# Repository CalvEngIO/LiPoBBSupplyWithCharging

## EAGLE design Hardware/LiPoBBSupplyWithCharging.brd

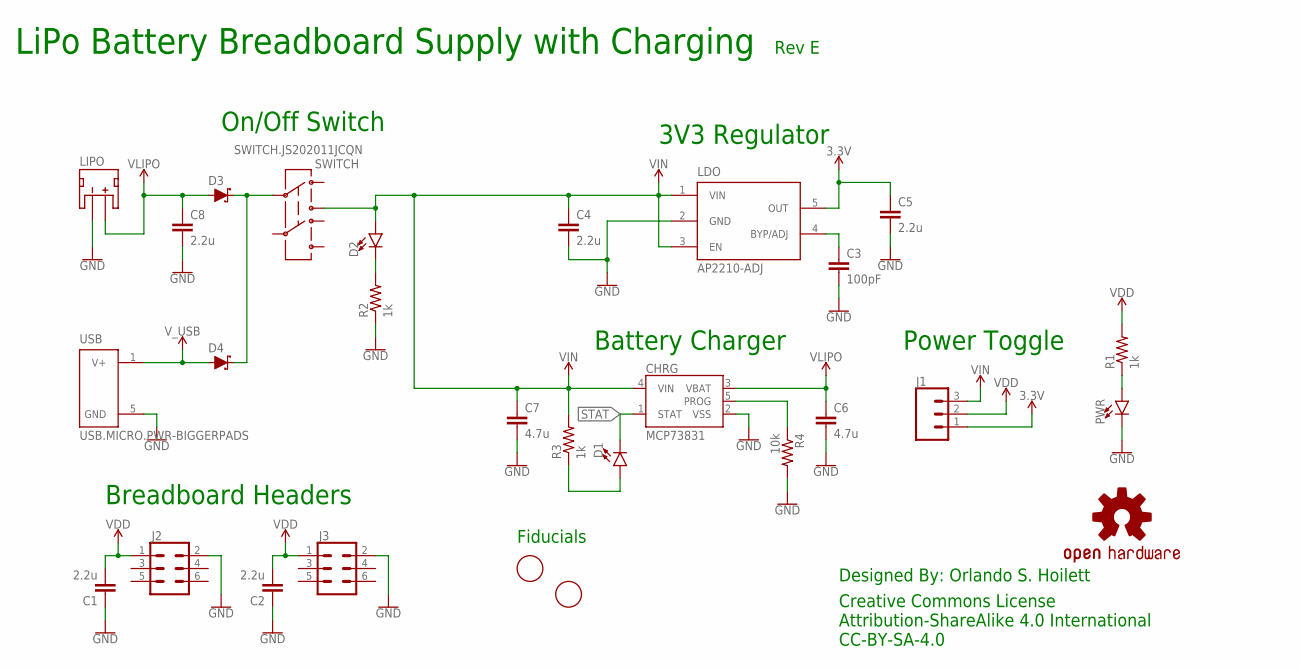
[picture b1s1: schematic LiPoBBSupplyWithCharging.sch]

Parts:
C1, C2, C4, C5, C8: 2.2u; C0603
C3: 100pF; C0402
C6, C7: 4.7u; C0603
CHRG: MCP73831; SOT23-5
D1, D2: LED0603; LED-0603
D3, D4: SCHOTTKY-USC; USC
FD1, FD2: FIDUCIAL; FIDUCIAL_1MM
J1: CONN_03; 1X03
J2, J3: CONN_03X22X3_SILK_MALE_PTH; 2X3
LDO: AP2210-ADJ; SOT23-5
LIPO: JST_2MM_MALE; JST-2-SMD
LOGO1: OSHW-LOGOS; OSHW-LOGO-S
PWR: LED0603; LED-0603
R1, R2, R3: 1k; R0402
R4: 10k; R0402
SWITCH: SWITCH.JS202011JCQN; SWITCH.00
U$1: HANDLE.1HANDLE.025; HANDLE.025
U$3: CALVENGIO_HANDLEHANDLE.1; CALVENGIO_HANDLE.1
USB: USB.MICRO.PWR-BIGGERPADS; USB-MICRO-01.BIGGERPADS.PWR

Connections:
3.3V: C5.1, J1.1, LDO.5 (OUT)
GND: C1.1, C2.1, C3.2, C4.2, C5.2, C6.2, C7.2, C8.2, CHRG.2 (VSS), J2.2, J3.2, LDO.2 (GND), LIPO.1 (-), PWR.C, R2.1, R4.2, USB.5 (GND)
unnamed: PWR.A, R1.1
unnamed: D2.C, R2.2
unnamed: C3.1, LDO.4 (BYP/ADJ)
unnamed: D1.A, R3.1
unnamed: CHRG.5 (PROG), R4.1
unnamed: D3.- (C), D4.- (C), SWITCH.2
STAT: CHRG.1 (STAT), D1.C
VDD: C1.2, C2.2, J1.2, J2.1, J3.1, R1.2
VIN: C4.1, C7.1, CHRG.4 (VIN), D2.A, J1.3, LDO.1 (VIN), LDO.3 (EN), R3.2, SWITCH.3
VLIPO: C6.1, C8.1, CHRG.3 (VBAT), D3.+ (A), LIPO.2 (+)
V_USB: D4.+ (A), USB.1 (V+)

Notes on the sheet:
Breadboard Headers
Power Toggle
3V3 Regulator
On/Off Switch
Fiducials
Creative Commons License Attribution-ShareAlike 4.0 International CC-BY-SA-4.0
Designed By: Orlando S. Hoilett
LiPo Battery Breadboard Supply with Charging
Battery Charger
Rev E

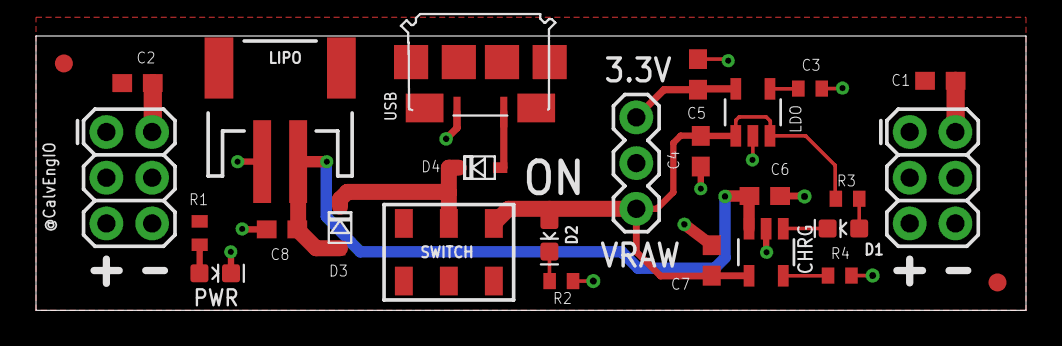
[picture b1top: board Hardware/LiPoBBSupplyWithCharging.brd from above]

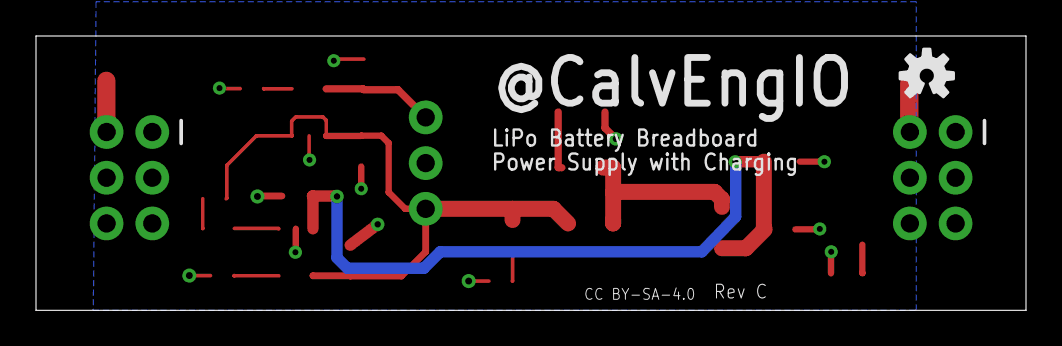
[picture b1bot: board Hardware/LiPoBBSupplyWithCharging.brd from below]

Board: 2 copper layers, 55.0 x 15.2 mm, 30 parts (2 on the bottom side), 13 nets.

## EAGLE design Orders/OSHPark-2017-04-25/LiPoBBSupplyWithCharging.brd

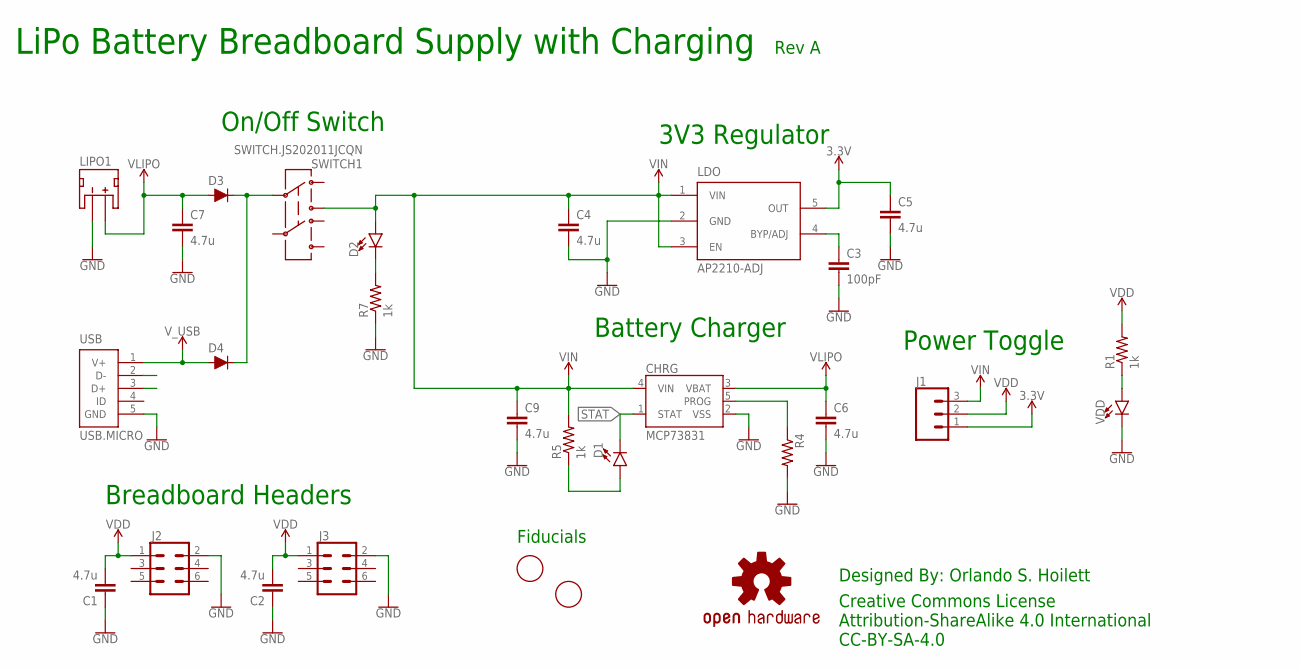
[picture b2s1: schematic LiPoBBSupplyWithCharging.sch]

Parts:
C1, C2, C4, C5, C6, C7, C9: 4.7u; C0603
C3: 100pF; C0402
CHRG: MCP73831; SOT23-5
D1, D2: LED0603; LED-0603
D3, D4: DIODE-BAS16J; SOD-323
FD1, FD2: FIDUCIAL; FIDUCIAL_1MM
J1: CONN_03; 1X03
J2, J3: CONN_03X22X3_SILK_MALE_PTH; 2X3
LDO: AP2210-ADJ; SOT23-5
LIPO1: JST_2MM_MALE; JST-2-SMD
LOGO1: OSHW-LOGOS; OSHW-LOGO-S
R1, R5, R7: 1k; R0402
R4: RESISTOR0402; R0402
SWITCH1: SWITCH.JS202011JCQN; SWITCH.00
U$1: HANDLE.1HANDLE.025; HANDLE.025
U$3: CALVENGIO_HANDLEHANDLE.1; CALVENGIO_HANDLE.1
USB: USB.MICRO; USB-MICRO-01
VDD: LED0603; LED-0603

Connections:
3.3V: C5.1, J1.1, LDO.5 (OUT)
GND: C1.1, C2.1, C3.2, C4.2, C5.2, C6.2, C7.2, C9.2, CHRG.2 (VSS), J2.2, J3.2, LDO.2 (GND), LIPO1.1 (-), R4.2, R7.1, USB.5 (GND), VDD.C
unnamed: R1.1, VDD.A
unnamed: D2.C, R7.2
unnamed: C3.1, LDO.4 (BYP/ADJ)
unnamed: D1.A, R5.1
unnamed: CHRG.5 (PROG), R4.1
unnamed: D3.C, D4.C, SWITCH1.2
STAT: CHRG.1 (STAT), D1.C
VDD: C1.2, C2.2, J1.2, J2.1, J3.1, R1.2
VIN: C4.1, C9.1, CHRG.4 (VIN), D2.A, J1.3, LDO.1 (VIN), LDO.3 (EN), R5.2, SWITCH1.3
VLIPO: C6.1, C7.1, CHRG.3 (VBAT), D3.A, LIPO1.2 (+)
V_USB: D4.A, USB.1 (V+)

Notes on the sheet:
Breadboard Headers
Power Toggle
3V3 Regulator
On/Off Switch
Fiducials
Creative Commons License Attribution-ShareAlike 4.0 International CC-BY-SA-4.0
Designed By: Orlando S. Hoilett
LiPo Battery Breadboard Supply with Charging
Battery Charger
Rev A

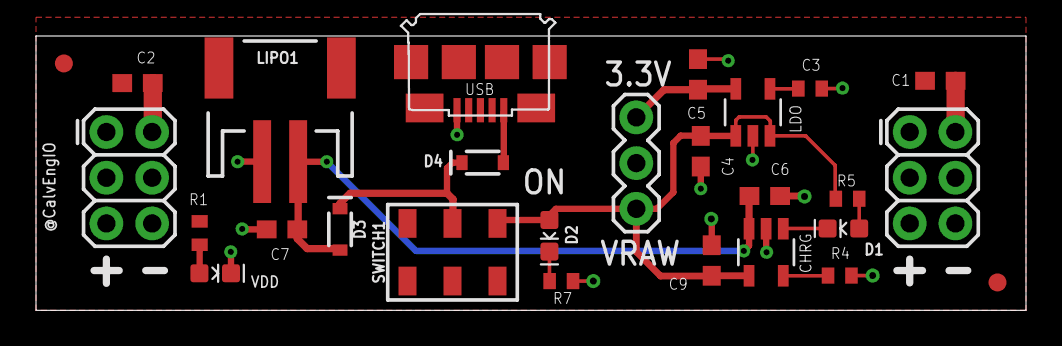
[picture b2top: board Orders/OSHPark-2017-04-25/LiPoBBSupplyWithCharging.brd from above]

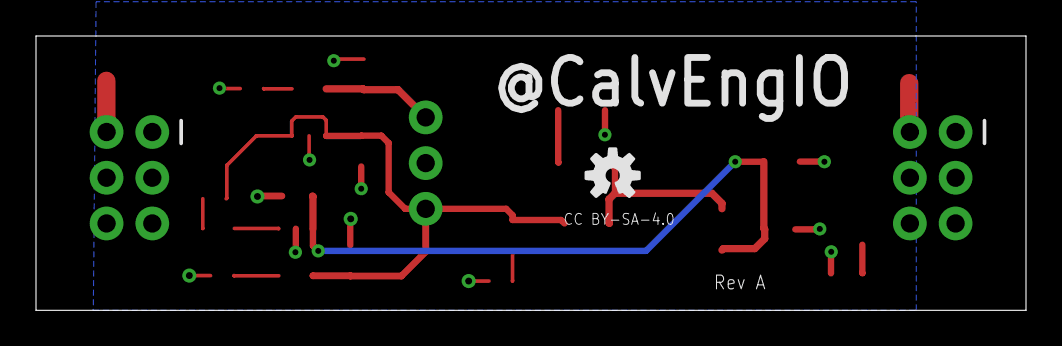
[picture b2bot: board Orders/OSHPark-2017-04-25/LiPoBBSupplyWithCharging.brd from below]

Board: 2 copper layers, 55.0 x 15.2 mm, 30 parts (2 on the bottom side), 13 nets.

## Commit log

2017-05-08 initial commit. lots of work to do
2017-05-08 Create LICENSE-Hardware

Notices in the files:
parts and their libraries:
SparkFun-Connectors: Licensing: Creative Commons ShareAlike 4.0 International - https://creativecommons.org/licenses/by-sa/4.0
